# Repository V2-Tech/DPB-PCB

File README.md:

<h1 align="center">Dynamic Propeller Balancer - PCBs</h1><br>

<div align="center">
    
</div>
<br>

## :mag: Description

Under development...

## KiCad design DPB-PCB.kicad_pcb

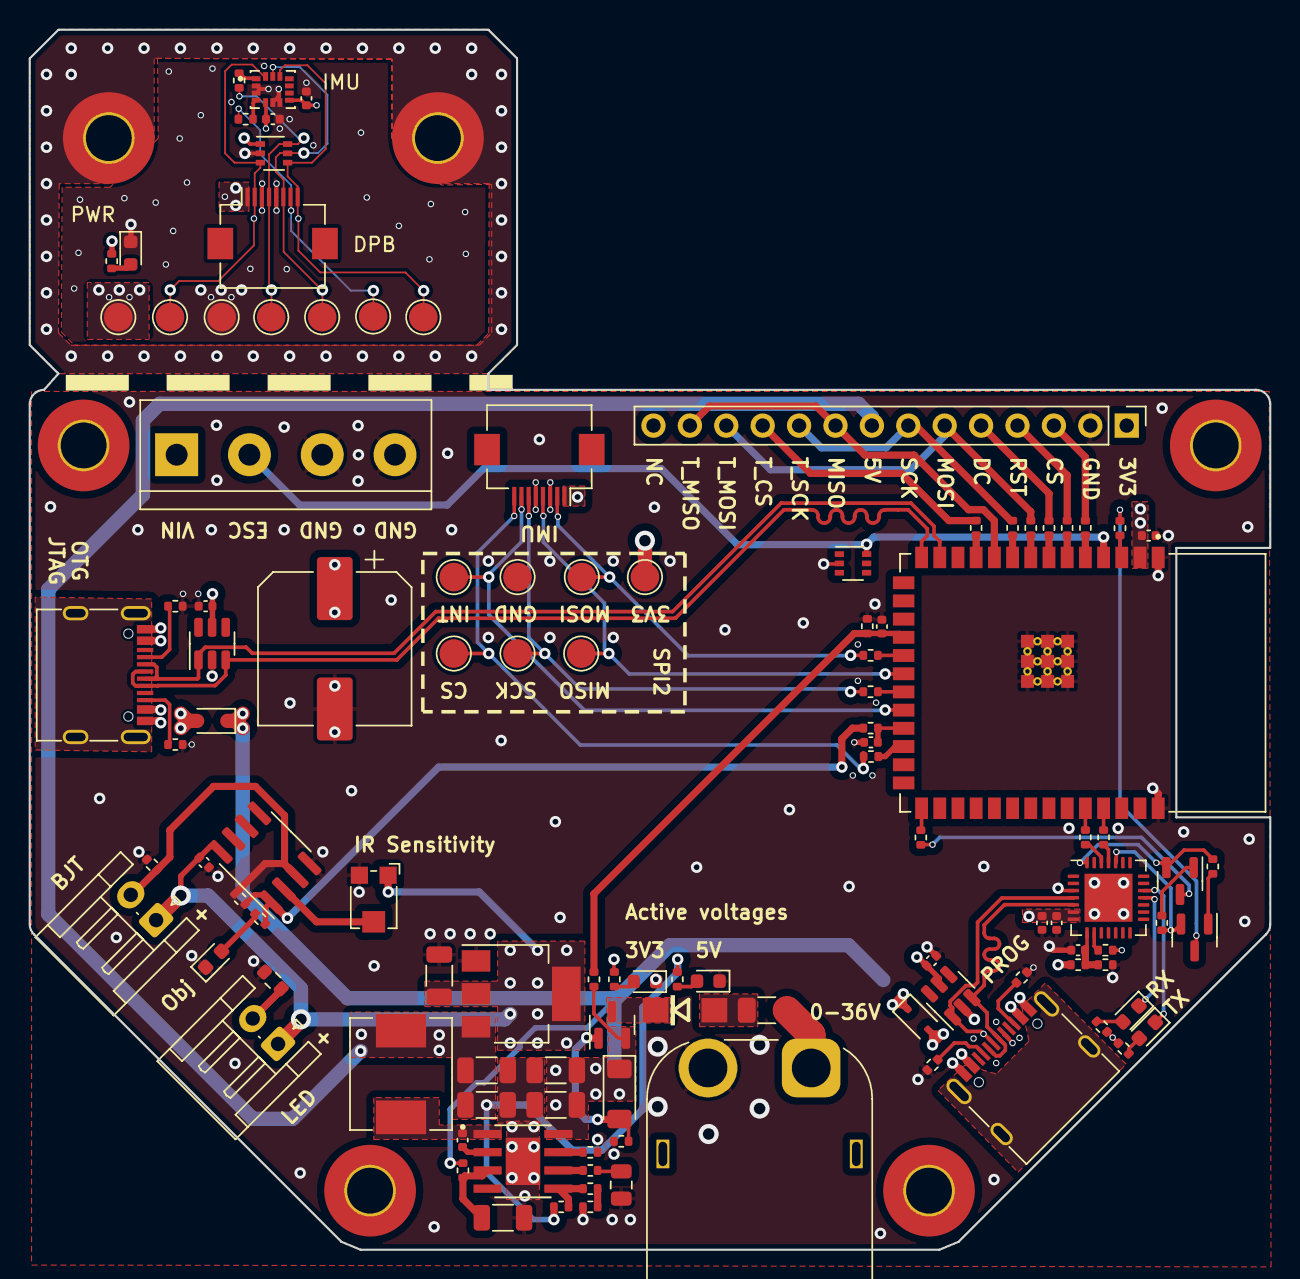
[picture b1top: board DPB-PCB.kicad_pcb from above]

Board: 4 copper layers, 86.6 x 85.1 mm, 118 parts (0 on the bottom side), 86 nets.

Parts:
3V1, 3V2: TestPoint_Pad_D2.0mm
C1, C2, C7, C12, C13, C15, C16, C17, C18, C19: 100n 50V; C_0402_1005Metric
C3, C4, C6, C10: 10u 50V; C_1206_3216Metric
C5: 2n2 50V; C_0805_2012Metric
C8, C9: 22u 10V; C_1206_3216Metric
C11, C14: 10u 6V3; C_0402_1005Metric
C21: 470uf 35V; CP_Elec_10x14.3
CS1, CS2: TestPoint_Pad_D2.0mm
D1, D11: LED_GREEN; LED_0603_1608Metric
D2: SS54; DO-214AC
D3, D7: LED_BLUE; LED_0603_1608Metric
D4: BZV55B5V6; D_MiniMELF
D5, D6: 1N5819WS; D_SOD-323
D8: LED_YLW; LED_0603_1608Metric
D9, D12: SMF05CT1G; SOT-363_SC-70-6
D10: LED_YELLOW; LED_0603_1608Metric
F1: 60V 120mA; Fuse_1206_3216Metric
GND1, GND2: TestPoint_Pad_D2.0mm
H1, H2, H3, H4, H5, H6: M3; MountingHole_3.2mm_M3_Pad_TopBottom
INT1, INT2: TestPoint_Pad_D2.0mm
J1: USB_C_Prog; USB_C_Receptacle_G-Switch_GT-USB-7010ASV
J2: LCD_Conn; PinHeader_1x14_P2.54mm_Vertical
J3, J9: IMU_FFC_Conn; Hirose_FH12-8S-0.5SH_1x08-1MP_P0.50mm_Horizontal
J4: IR_SENSOR; JST_EH_S2B-EH_1x02_P2.50mm_Horizontal
J5: ESC_Conn; TerminalBlock_bornier-4_P5.08mm
J6: IR_LED; JST_EH_S2B-EH_1x02_P2.50mm_Horizontal
J7: XT60 - M; AMASS_XT60PW-M_1x02_P7.20mm_Horizontal
J8: USB_C_OTG; USB_C_Receptacle_G-Switch_GT-USB-7010ASV
L1: 6u8; L_Chilisin_BMRx00060630
MISO1, MISO2: TestPoint_Pad_D2.0mm
MOSI1, MOSI2: TestPoint_Pad_D2.0mm
Q1: AO3401A; SOT-23
Q2, Q3: MMBT5551; SOT-23
R1, R4, R5, R6, R7, R8, R9, R41, R42: 47; R_0402_1005Metric
R2, R3: 100; R_0402_1005Metric
R10, R12, R14, R29, R30, R33, R38, R39, R40: 1k; R_0402_1005Metric
R11, R19, R21, R22, R37: 10k; R_0402_1005Metric
R13: 3k3; R_0402_1005Metric
R15: 33k; R_0402_1005Metric
R16: 5k6; R_0402_1005Metric
R17: 680; R_0402_1005Metric
R18: 24k; R_0402_1005Metric
R20: 130k; R_0402_1005Metric
R23, R24: 0; R_0402_1005Metric
R25, R26, R34, R35: 5k1; R_0402_1005Metric
R27: 56k; R_0402_1005Metric
R28: 120k; R_0402_1005Metric
R31, R32: 10; R_0402_1005Metric
R36: 100; R_0603_1608Metric
R43: 100k; R_0402_1005Metric
RV1: 10k; Potentiometer_Bourns_TC33X_Vertical
SCK1, SCK2: TestPoint_Pad_D2.0mm
U1: ESP32-S3-WROOM-1-N4R2; XCVR_ESP32-S3-WROOM-1-N4R2
U2: RT7272BGSP; SOIC127P599X175-9N
U3: AMS1117-3.3; SOT-223-3_TabPin2
U4, U6: USBLC6-4SC6; SOT-23-6
U5: CP2102N-Axx-xQFN28; QFN-28-1EP_5x5mm_P0.5mm_EP3.35x3.35mm
U7: LM358; SOIC-8_3.9x4.9mm_P1.27mm
U8: LSM6DSLTR; PQFN50P300X250X86-14N

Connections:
+3.3V: 3V1.1, C1.1, C10.1, C13.1, C14.1, C16.1, J2.1, J3.1, J4.1, J6.1, R14.2, R29.1, R30.2, R33.2, RV1.1, U1.2 (3V3), U3.2 (VO), U5.6 (VDD), U5.7 (VREGIN), U7.8 (V+)
+5V: C8.1, C9.1, J2.8, L1.2, R10.2, R15.1, U3.3 (VI)
+VDC: C21.1, F1.1, J5.1, J7.1
/BOOT: R24.2, U1.27 (IO0)
/EN: R23.2, U1.3 (EN)
/GPIO5: R1.1, U1.5 (IO5)
/GPIO6: R2.1, U1.6 (IO6)
/GPIO7: R3.1, U1.7 (IO7)
/GPIO11: R4.1, U1.19 (IO11)
/GPIO13: R5.1, U1.21 (IO13)
/GPIO15: R6.1, U1.8 (IO15)
/GPIO16: R7.1, U1.9 (IO16)
/GPIO18: R8.2, U1.11 (IO18)
/GPIO47: R9.2, U1.24 (IO47)
/IMU/3V3: 3V2.1, C18.1, C19.1, D12.1 (K), J9.1, R40.2, U8.5 (VDDIO), U8.8 (VDD)
/IMU/CS: CS2.1, D12.4 (K), J9.8, U8.12 (CS)
/IMU/INT1: INT2.1, J9.7, R42.1
/IMU/MISO: D12.6 (K), J9.4, MISO2.1, R41.2
/IMU/MOSi: D12.3 (K), J9.2, MOSI2.1, U8.14 (SDA)
/IMU/SCK: D12.5 (K), J9.6, SCK2.1, U8.13 (SCL)
/Power Supply/BOOT: C7.2, U2.2 (BOOT)
/Power Supply/COMP: R18.1, U2.6 (COMP)
/Power Supply/EN: C6.1, R19.2, U2.3 (EN)
/Power Supply/FB: R15.2, R16.1, U2.5 (FB)
/Power Supply/SW: C7.1, L1.1, U2.1 (SW)
/RXD0: R31.2, U1.36 (RXD0)
/TXD0: R32.2, U1.37 (TXD0)
/USB/D+: J1.A6 (D+), J1.B6 (D+), U4.1 (I/O1), U5.4 (D+)
/USB/D-: J1.A7 (D-), J1.B7 (D-), U4.3 (I/O2), U5.5 (D-)
/USB/DTR: Q3.2 (E), R21.1, U5.28 (~DTR)
/USB/RTS: Q2.2 (E), R22.1, U5.24 (~RTS)
/USB/RXD: R32.1, U5.25 (RXD)
/USB/RXT: D7.1 (K), U5.18 (~RXT/GPIO.1)
/USB/TXD: R31.1, U5.26 (TXD)
/USB/TXT: D8.1 (K), U5.19 (~TXT/GPIO.0)
ESC_CMD: D9.6 (K), J5.2, U1.4 (IO4)
Earth_Protective: H5.1, H6.1
GND: C1.2, C2.2, C3.2, C4.2, C5.2, C6.2, C8.2, C9.2, C10.2, C11.2, C12.2, C13.2, C14.2, C15.2, C16.2, C17.2, C21.2, D1.1 (K), D3.1 (K), D9.2 (A), D10.1 (K), GND1.1, J1.A1 (GND), J1.A12 (GND), J1.B1 (GND), J1.B12 (GND), J2.2, J3.3, J3.5, J5.3, J5.4, J7.2, J8.A1 (GND), J8.A12 (GND), J8.B1 (GND), J8.B12 (GND), R12.1, R13.2, R17.2, R20.2, R25.2, R26.2, R28.2, R34.2, R35.2, R36.1, R37.1, RV1.3, U1.1 (GND), U1.40 (GND), U1.41 (GND), U2.4 (GND), U2.9 (PAD), U3.1 (GND), U4.2 (GND), U5.3 (GND), U5.29 (GND), U6.2 (GND), U7.4 (V-)
GND2: C18.2, C19.2, D11.1 (K), D12.2 (A), GND2.1, J9.3, J9.5, U8.2 (SDX), U8.3 (SCX), U8.6 (GND), U8.7 (GND)
IMU_CS: CS1.1, J3.8, R9.1
IMU_INT: INT1.1, J3.7, U1.22 (IO14)
IMU_MISO: J3.4, MISO1.1, U1.20 (IO12)
IMU_MOSI: J3.2, MOSI1.1, R4.2
IMU_SCK: J3.6, R5.2, SCK1.1
IR_INTERRUPT: C17.1, R39.2, U1.23 (IO21)
IR_LED_K: J6.2, R36.2
IR_SENSE_A: J4.2, R37.2, R43.1, U7.3 (+)
LCD_CS: J2.3, R1.2
LCD_DC: J2.5, R3.2
LCD_MISO: J2.9, J2.13, U1.10 (IO17)
LCD_MOSI: J2.6, J2.12, R6.2
LCD_RESET: J2.4, R2.2
LCD_SCK: J2.7, J2.10, R7.2
LCD_T_CS: J2.11, R8.1
unnamed: C5.1, R18.2
unnamed: D1.2 (A), R10.1
unnamed: D2.A, F1.2
unnamed: D3.2 (A), R14.1
unnamed: D4.2 (A), Q1.1 (G), R13.1
unnamed: D7.2 (A), R30.1
unnamed: D8.2 (A), R33.1
unnamed: D10.2 (A), R38.1
unnamed: D11.2 (A), R40.1
unnamed: J1.A5 (CC1), R25.1
unnamed: J1.B5 (CC2), R26.1
unnamed: J8.A5 (CC1), R34.1
unnamed: J8.B5 (CC2), R35.1
unnamed: D2.C, Q1.3 (D)
unnamed: Q2.1 (B), R21.2
unnamed: Q2.3 (C), R23.1
unnamed: Q3.1 (B), R22.2
unnamed: Q3.3 (C), R24.1
unnamed: R16.2, R17.1
unnamed: R38.2, R39.1, R43.2, U7.1
unnamed: R20.1, U2.7 (RLIM)
unnamed: C11.1, R27.2, R28.1, U5.8 (VBUS)
unnamed: R29.2, U5.9 (~RST)
unnamed: RV1.2, U7.2 (-)
unnamed: R42.2, U8.4 (INT1)
unnamed: R41.1, U8.1 (SDO/SA0)
USB_D+: J8.A6 (D+), J8.B6 (D+), U1.14 (IO20), U6.3 (I/O2)
USB_D-: J8.A7 (D-), J8.B7 (D-), U1.13 (IO19), U6.1 (I/O1)
VBUS: C12.1, D5.2 (A), J1.A4 (VBUS), J1.A9 (VBUS), J1.B4 (VBUS), J1.B9 (VBUS), R27.1, U4.5 (VBUS)
VCC: C3.1, C4.1, D4.1 (K), D5.1 (K), D6.1 (K), Q1.2 (S), R11.1, R19.1, U2.8 (VIN)
V_ADC2: C2.1, R11.2, R12.2, U1.18 (IO10)
V_USB: C15.1, D6.2 (A), J8.A4 (VBUS), J8.A9 (VBUS), J8.B4 (VBUS), J8.B9 (VBUS), U6.5 (VBUS)

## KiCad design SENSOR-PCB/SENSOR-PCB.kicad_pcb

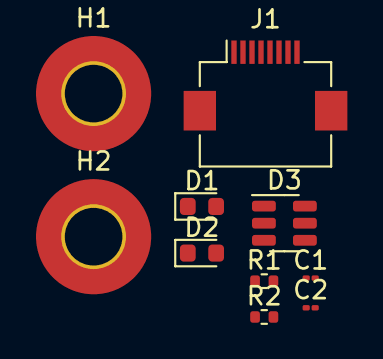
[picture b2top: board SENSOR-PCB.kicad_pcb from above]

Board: 2 copper layers, 10 parts (0 on the bottom side), 9 nets, no tracks yet.

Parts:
C1, C2: 100n 50V; C_01005_0402Metric
D1: LED_GREEN; LED_0603_1608Metric
D2: LED_BLUE; LED_0603_1608Metric
D3: SMF05CT1G; SOT-23-6
H1, H2: M3; MountingHole_3.2mm_M3_Pad_TopBottom
J1: IMU_FFC_Conn; Hirose_FH12-8S-0.5SH_1x08-1MP_P0.50mm_Horizontal
R1, R2: 1k; R_0402_1005Metric

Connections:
/3V3: C1.1, C2.1, D3.1 (K), J1.1, R1.2
/CS: D3.6 (K), J1.8
/INT1: J1.7, R2.2
/MISO: D3.3 (K), J1.4
/MOSi: D3.4 (K), J1.2
/SCK: D3.5 (K), J1.6
GND2: C1.2, C2.2, D1.1 (K), D2.1 (K), D3.2 (A), J1.3, J1.5
unnamed: D1.2 (A), R1.1
unnamed: D2.2 (A), R2.1

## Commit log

2023-02-24 Create project
2023-02-24 Add ESP WROOM and USB-C
2023-03-14 All components have been added
2023-03-15 Divided project
2023-03-15 Sensor board has its own project
2023-03-22 DPB mainboard_v1 completed
2023-03-23 Align mech holed
2023-03-24 On production | V0.1
2023-03-25 Edge cut changed to avoid supplement fee
2023-03-30 Add hysteresis to IR sensor. Update README file.
2023-03-30 README update
